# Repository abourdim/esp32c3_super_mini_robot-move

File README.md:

# 🤖 esp32c3_super_mini_robot-move — b3 on the `30_esp32_c3_move` board

A port of [`esp32c3_super_mini_robot-bit-rxy`](https://github.com/abourdim/esp32c3_super_mini_robot-bit-rxy)
("b3") onto the **`30_esp32_c3_move`** carrier board, plus a panning sonar head
the original does not have. Driven over Bluetooth Low Energy from the
[rxy web app](https://github.com/abourdim/rxy_web) — no install, no account, no
WiFi.

**The robot owns the layout.** The app is a generic renderer: it connects, asks
the robot for its panel, and draws whatever comes back. There is no per-robot
build of the app.

## Faithful to b3

Every module b3 has is still in the tree — buzzer, NeoPixels, battery sense,
board LEDs, OLED, both NeoPixel demos, all eight panels. Nothing was deleted.
What changed is the pin map, because the two carrier boards share an MCU and
nothing else.

What is **not fitted** on this build is switched off at a single `#define`
each, so it compiles out rather than failing at runtime:

| feature | b3 | here | state |
|---|---|---|---|
| left / right drive servo | GPIO 6 / 3 | **5 / 10** — J5 / J12, level-shifted | ✅ |
| HC-SR04 | 21 / 20 | **6 / 7** — J10, level-shifted | ✅ |
| head servo | *(none)* | **1** — J6 | ✅ |
| button / OTA | 0 (module BOOT) | **3** — SW1 | ✅ |
| green / red LED | 1 / 10 | **0 / 21** — J7 / J8 | ✅ |
| NeoPixel strip | 5 (or 10) | 20 — J9 | `CONFIG_NEOPIXELS_ENABLED 0` |
| buzzer | 4 | 4 — SW2 pads | `CONFIG_BUZZER_ENABLED 0` |
| battery sense | 4 | 4 — SW2 pads, **no divider on the board** | reads meaningless |
| OLED | I²C 8 / 9 | 8 / 9 — module pads, **not wired** | `CONFIG_OLED_ENABLED 0` |

Turning the strip off is worth more than it looks: its default French-flag
effect calls `delay(1000/60)` on **every** `loop()` iteration, so an absent
strip still paced the whole robot at 60 Hz to animate nothing.

The OLED keeps its runtime presence-probe for the day the wires go on, but with
the feature off nothing touches the I²C bus at all — not even the five-second
re-probe, which would otherwise poke a dead bus forever. Set
`CONFIG_OLED_ENABLED 1` once SDA/SCL/3V3/GND are on the module's pads; nothing
else needs changing. Wiring and the strapping-pin reasoning:
[`02_hardware/README.md`](02_hardware/README.md#attaching-the-oled).

Board source and the full netlist-derived pin map: [`02_hardware/`](02_hardware/).

## Three servos need four PWM timers

b3 allocates **one** LEDC timer and attaches two servos, which exactly fits.
The head makes three, and ESP32Servo does not warn when it runs short — it
prints `All PWM timers allocated! Can't accomodate 50.000 Hz` and **halts
inside `attach()`**, so `setup()` never returns.

That failure is invisible from outside. NimBLE has already started on its own
task by then, so the robot still advertises and the app still connects; it just
never answers anything, because `remotexy_handler()` lives in `loop()` and
`loop()` has never run. It presents as a protocol bug and is not one.

`setup()` now allocates all four.

## The 3-pin headers double as FET gates

J6, J7, J8 and J9 carry the same nets as Q1–Q4's gates, which drive the J1–J4
screw terminals and their yellow indicator LEDs. Anything plugged into a 3-pin
header switches its paired screw terminal in sympathy, so **leave J1–J4
unpopulated**. The upside is free activity indicators: D6–D9 light along with
whatever is on the header, so the link LEDs are visible even with nothing
plugged in.

## Why the button moved off GPIO 0

b3 uses the SuperMini's own BOOT button for the three-second OTA hold, and that
button exists here too. But on this board GPIO 0 is Q2's gate, so the gesture
would switch the J2 output on for the length of the hold — and GPIO 0 is more
useful as the green LED. SW1 is a real button with its own pull-up that drives
nothing else.

## Drive direction

`CONFIG_SERVO_INVERT_DRIVE` flips both channels. Both wheels ran backwards on
this chassis — that is motor polarity, not a left/right mix-up, and swapping
the two pins would have given a robot that spins instead. The flip is applied
to the command before the mix becomes pulses, so trim and the speed cap stay in
the frame they were written for, and it corrects the steering with it: with the
polarity wrong, a spin-left command was coming out as spin-right.

## The head, the radar, and sweep

The head servo is the one thing here that b3 does not have. It gives the app's
**radar** widget a bearing to plot against — the radar carries no value of its
own, it reads the distance gauge and the head slider by id.

**Sweep** is a toggle in the DISTANCE group. The head steps one notch per
telemetry pass rather than on a timer of its own, and the step happens *after*
the pass has sent this cycle's distance and angle. That ordering is the point:
the radar plots (angle, distance) pairs, and stepping independently would paint
readings at bearings the sensor was not pointing at when they were taken. Each
step then gets a full 500 ms to settle before the next measurement. 15° steps
across 10–170° is about 5.5 s per sweep.

Reversal happens **at** each limit, not past it. `moveHead()` clamps anyway,
but bouncing off the clamp parks the head on its end stop for an extra pass
every sweep — a stutter on the scope, and a stalled servo while it lasts.

Dragging the slider takes the head off sweep, otherwise the servo fights you
and the slider snaps back on the next pass. Leaving sweep re-centres.

The bearing is published every telemetry pass. Without that the radar plots at
whatever `head` last reported, which was its default — the head would sweep and
the scope would show a beam frozen at 90°.

**Head trim** (`head_off`, plus H−1 / H+1 buttons) is mechanical centring: a
pan mount is glued or screwed on by hand, so commanding 90° almost never points
dead ahead. The offset is applied where the servo is *written*, not to the
bearing that gets reported — the radar has to plot where the sensor is really
aimed, which is the corrected direction. Like the wheel trims it lives in NVS,
because it describes how the robot was assembled rather than how it is being
driven; and like them it rides the save-settle, so dragging the slider across
its range costs one flash write rather than sixty.

`CONFIG_SERVO_HEAD_MIN` / `_MAX` are the **mechanical** limits of your pan
mount, not 0–180. Narrow them to what the mount clears — a servo told to go
past its stop sits there stalled, drawing full stall current off the same rail
as the C3.

## Panels

b3's eight, plus a ninth — **Radar** — switched with the **Level** selector;
the choice is kept in NVS. The Radar panel is one subsystem on its own: the
scope, the head slider, Sweep, the head trim, and the distance readout the
radar is plotting, so the panel explains itself — you can see the number each
blip came from.

The new level is appended to the enum rather than inserted, because the level
index lives in NVS: renumbering the existing entries would silently move an
upgraded robot to a different panel. And since every layout carries its own
copy of the selector's options, all nine blobs were rewritten — otherwise the
new level would be unreachable from wherever you happened to be.

Expert has been cut down to what this board actually has:

- **removed** — the DISPLAY group (no OLED) and the SOUND group (no buzzer)
- **removed** — the six strip widgets from LIGHTS; the two board LEDs stay,
  they are real, and their J7/J8 headers light the onboard yellows too
- **moved** — TRIM is no longer its own group; all eight widgets sit inside
  DRIVE, which is where you use them, tuning while driving and watching the pull
- **added** — the head slider, the sweep toggle, and the radar, in DISTANCE

> ⚠️ **`gen_test_layouts.py` writes `test_decls.h`, which nothing includes.**
> The live blobs are hardcoded in `03_bit-rxy.cpp`, so running the generator
> changes nothing that reaches the board. It needs a splice step — S2's
> `gen_layouts.py` has the logic to copy — or it should be deleted. Until then,
> layout edits go into the blobs directly.

## Build and flash

```bash
cd 01_software/01_app && pio run -e esp32-c3-devkitm-1 -t upload
```

After the first USB flash, hold **SW1 for 3 seconds** to enter WiFi OTA mode.
Hold to 8 seconds to forget the saved network. The device is reachable as
`wdiy-move`, and the setup AP is `WDIY-Robot-Setup`.

BLE device name is `diy_app_mv`, distinct from b3's `diy_app_b3` so the two are
told apart in the scanner when both are powered on in the same room.

**The image is at 91.5% of flash** — roughly 110 KB spare on the default
partition table. Enough for tuning, not for another subsystem.

Note that with native USB-CDC the serial monitor attaches *after* boot, so you
will usually see nothing at startup. That is normal, not a fault.

## Before you build one

Three board facts firmware cannot paper over — the long form is in
[`02_hardware/README.md`](02_hardware/README.md):

- **J1–J4 must stay unpopulated** while anything is on J6–J9. Same nets.
- **J6 has no level shifter.** J5, J12 and J10 run through the TXB0104 and get
  clean 5 V logic; J6 carries the raw 3.3 V pin. Most hobby servos accept that.
- **The servo rail needs 470–1000 µF** at the connectors, fed from the input
  terminal rather than through the SuperMini's 5 V pin. Three drive servos on a
  rail with 100 nF browns the C3 out mid-drive, which reads as a random reboot.

## Known issues

- **Trim is applied with the wrong sign**, inherited from b3. It is added to
  both wheels, but the right channel's pulse range is inverted, so a positive
  trim pushes the two wheels in *opposite* physical directions. With b3's
  defaults of `5`/`5` an idle robot slowly rotates on the spot. Either zero the
  two `CONFIG_SERVO_SPEED_STOP_*_OFFSET` values or port S2's fix (`10c1468`),
  which subtracts on the inverted side.
- **`01_software/01_app/02_web/`** is b3's site and still describes b3's pin
  map. Its Pages workflow is set to manual trigger only, so a push cannot
  publish a site that is wrong about this robot. Rewrite it before re-enabling.

## Wiki

A full illustrated walkthrough — clone, build, flash, verify, plus the board's
pin map and how the sweep is paced — is on the wiki in three languages:

- [Robot MV (English)](https://abourdim.github.io/wiki/robot-mv-en.html)
- [Robot MV (Français)](https://abourdim.github.io/wiki/robot-mv.html)
- [Robot MV (العربية)](https://abourdim.github.io/wiki/robot-mv-ar.html)

Powered by [Workshop-DIY.org](https://workshop-diy.org)

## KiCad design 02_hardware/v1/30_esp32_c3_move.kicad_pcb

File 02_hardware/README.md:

# 🔌 Hardware

KiCad source, PCB renders and fab output for **`30_esp32_c3_move`**, the board
this firmware targets. Upstream lives at `01_kicad/30_esp32_c3_move/`.

## Versions

| Version | Status | Folder |
|---|---|---|
| **v1** | ✅ **Current — fabricated, and what the firmware is written against** | [`v1/`](v1/) |
| v2 | 📝 Planning stub, not a revision | [`v2/`](v2/) |

**v2 is not a new board.** Its PCB is byte-identical to v1 and it carries the
same 98 components; the only differences are one schematic block nudged 14 mm,
a project rename, and a to-do note dated 02/06/2025:

> add 2 neo pixel · oled connector · buzzer · battery level · large soldering
> footprint for the transistor

None of those are implemented. It is kept here because it is where that plan is
written down, not because it builds anything different.

## The pin map, and where it came from

Read out of `v1/30_esp32_c3_move.kicad_pcb` by walking footprint pads to nets —
**not** from the schematic, which labels every net `gpio_NN` and records nothing
about what it drives. `00_config.h` is the firmware-side copy of this table.

| GPIO | Connector | Used for |
|---|---|---|
| 5 | J5, 3-pin, via TXB0104 | left drive servo |
| 10 | J12, 3-pin, via TXB0104 | right drive servo |
| 6 / 7 | J10, 4-pin, via TXB0104 | HC-SR04 trig / echo |
| 1 | J6, 3-pin, **raw 3.3 V** · also Q1 gate → J1 | head servo |
| 0 | J7, 3-pin · also Q2 gate → J2 | green LED |
| 21 | J8, 3-pin · also Q3 gate → J3 | red LED |
| 20 | J9, 3-pin · also Q4 gate → J4 | NeoPixel strip |
| 3 | SW1, 10k pull-up R10 | button, OTA hold |
| 4 | SW2, 10k pull-up R11 | 🔧 buzzer + battery sense, bodged to the pads |
| **2, 8, 9** | **nowhere — module pads only** | 🔧 OLED on 8/9, four wires |

The four 3-pin headers are the same nets as the FET gates, so anything on
J6–J9 switches its paired screw terminal too. **Leave J1–J4 unpopulated.** The
compensation is that D6–D9 become free activity indicators for whatever is on
the header.

Each switched output has a 1N4007 flyback (D1–D4), a 10k gate pull-down
(R6–R9) and a yellow state LED (D6–D9 + R1–R4). The SK12D07VG4 slide switch
gates the input rail; J11 (screw) and J13 (JST-PH) both feed it.

## Three things to know before building one

**The 3-pin headers share nets with the screw terminals.** GPIO 1 is Q1's gate
*and* J6's signal pin; the same pairing holds for J7/J2, J8/J3 and J9/J4. A
servo on J6 pulses the J1 output at 50 Hz and flickers D6 continuously; a load
on J1 makes the head twitch. Populate the header or the terminal, never both.
Firmware cannot arbitrate this — it is a copper fact.

**J6 has no level shifter.** J5, J12 and J10 all run through the TXB0104 and
get clean 5 V logic. J6 carries the raw 3.3 V pin. Most hobby servos accept
that; a fussy one is the case where this board bites.

**The servo rail needs bulk capacitance.** Three servos share `VCC` with the
ESP32 and v1 has only 100 nF on that rail. An SG90 pulls ~700 mA stalled with
a larger startup surge, and these are drive servos — they run constantly. Add
**470–1000 µF at the servo connectors**, and feed servo power straight from the
input terminal rather than through the SuperMini's 5 V pin, so servo current
does not run through the module. Without this the rail dips and the C3 browns
out mid-drive, which reads as a random reboot.

## Attaching the OLED

GPIO 2, 8 and 9 reach the SuperMini's pads and no connector, so the SSD1306 is
four wires soldered to the module itself. This is what v2's "oled connector"
note is meant to fix.

| OLED pin | goes to |
|---|---|
| SDA | module **GPIO 8** |
| SCL | module **GPIO 9** |
| VCC | module **3V3** — *not* 5V, see below |
| GND | any GND |

**Take VCC from 3V3, not 5V.** Most SSD1306 modules accept either, but the
module's own I2C pull-up resistors go to whatever you feed it. On 5V those
pull-ups would hold SDA and SCL at 5V, and the C3's GPIOs are not 5V tolerant.

**The pull-ups are also what make the board boot.** GPIO 8 and 9 are both
strapping pins on the ESP32-C3, and both need to be high at reset — GPIO 9 low
at reset is what selects download mode. The module's pull-ups hold them there,
which is exactly why this pin pair works on b3 too. Flashing still works
normally: the module's BOOT button pulls GPIO 9 low against the pull-up.

The firmware probes `0x3C` at boot and re-probes every five seconds while no
screen is answering, so a wire that makes contact late or works loose recovers
without a power cycle. Watch serial for `[OLED] found` or `[OLED] appeared on
the bus`. If you get neither, the usual cause is a module strapped to **0x3D**
instead of 0x3C — some boards have a solder jumper for it.

Powered by [Workshop-DIY.org](https://workshop-diy.org)

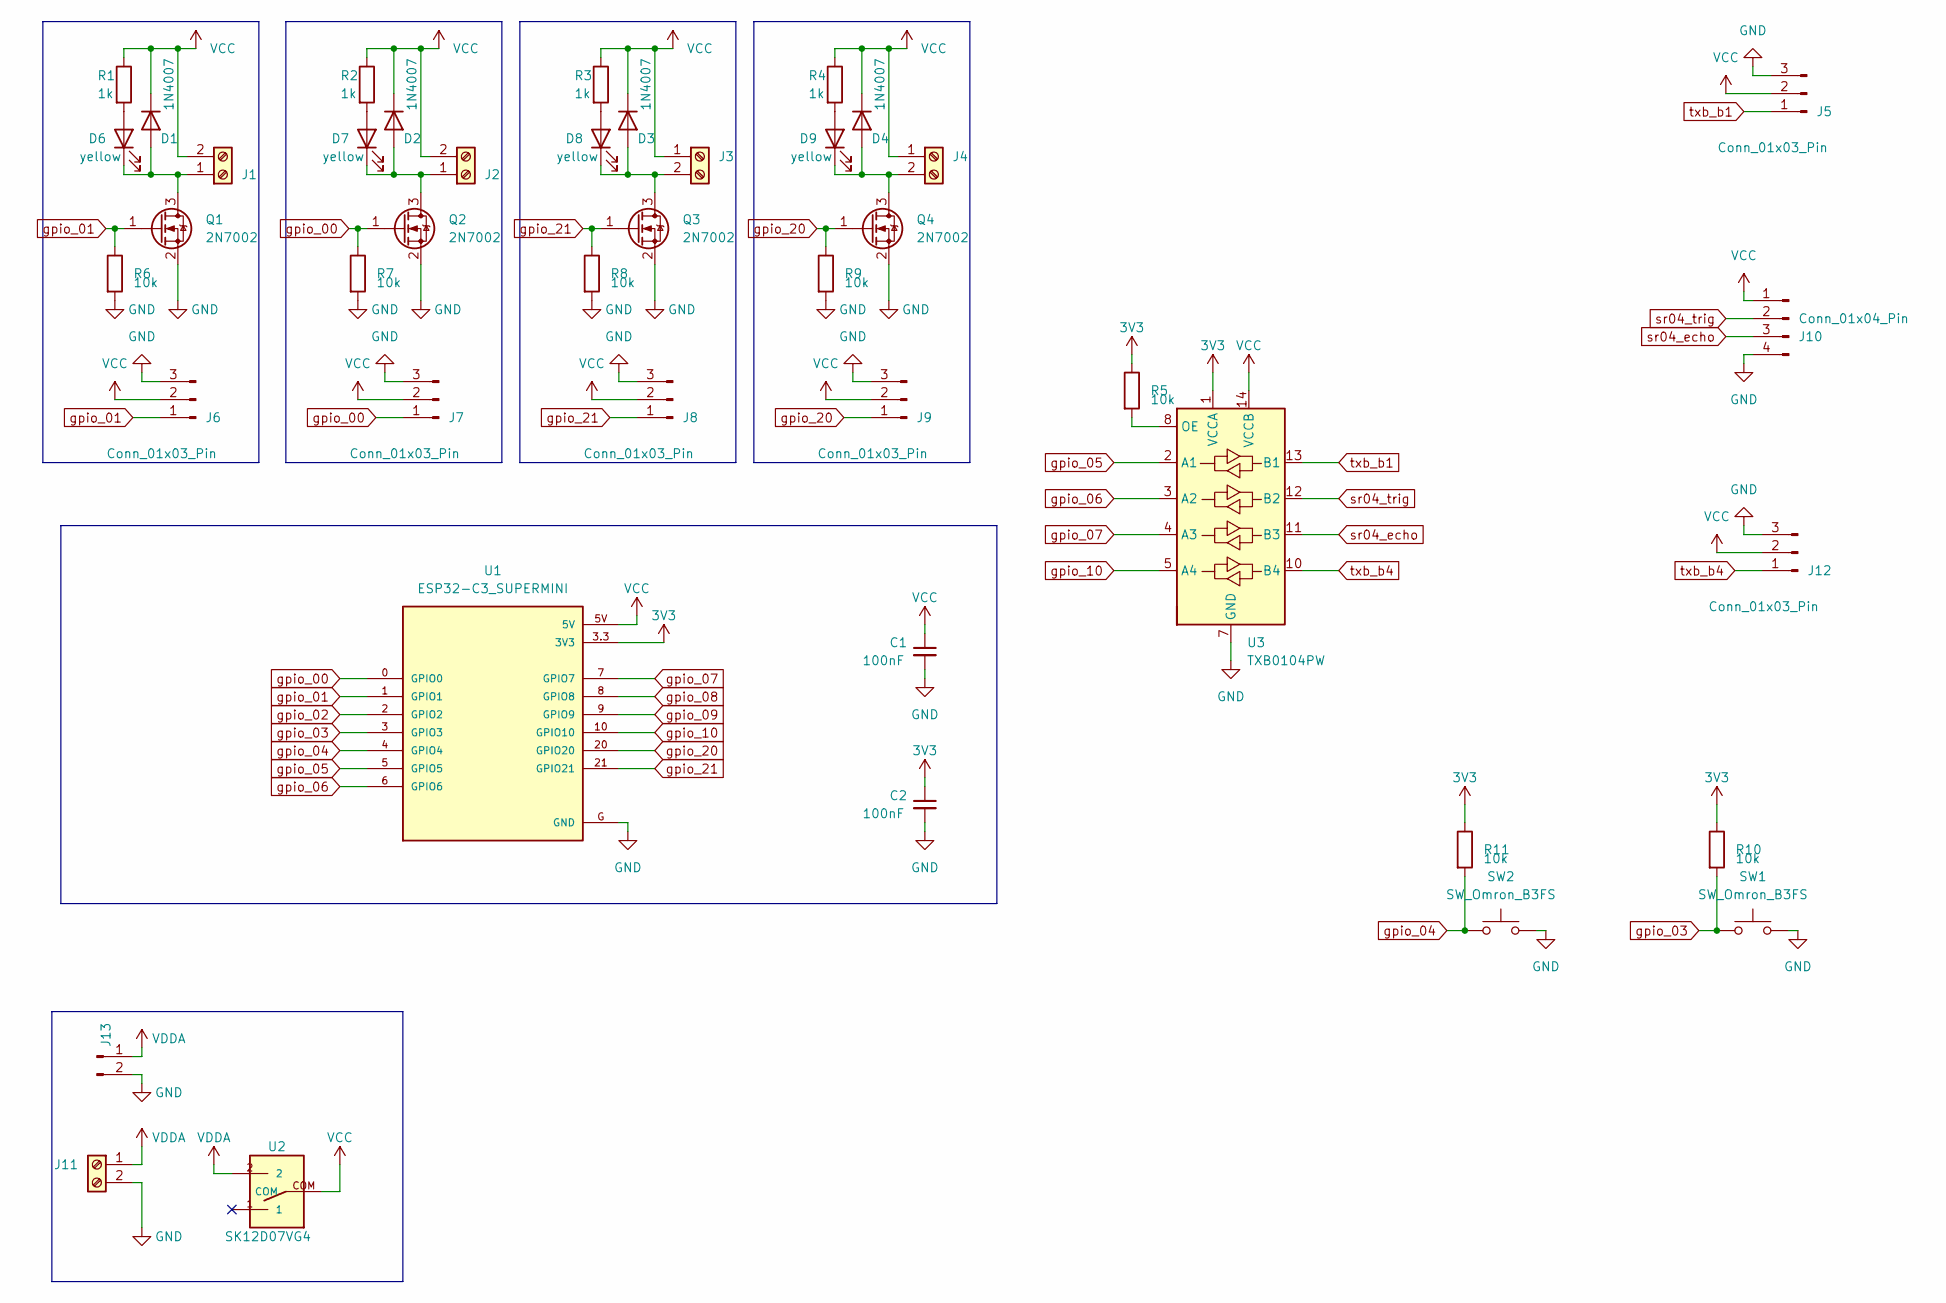
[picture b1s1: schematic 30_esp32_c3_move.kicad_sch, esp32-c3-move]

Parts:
C1, C2: 100nF; C_0805_2012Metric
D1, D2, D3, D4: 1N4007; D_SOD-123F
D6, D7, D8, D9: yellow; LED_0805_2012Metric_Pad1.15x1.40mm_HandSolder
J1, J2, J3, J4, J11: Screw_Terminal_01x02; TerminalBlock_Phoenix_MPT-0,5-2-2.54_1x02_P2.54mm_Horizontal
J5, J6, J7, J8, J9, J12: Conn_01x03_Pin; PinHeader_1x03_P2.54mm_Vertical
J10: Conn_01x04_Pin; PinHeader_1x04_P2.54mm_Vertical
J13: Conn_01x02_Pin; JST_PH_S2B-PH-K_1x02_P2.00mm_Horizontal
Q1, Q2, Q3, Q4: 2N7002; SOT-23_Handsoldering
R1, R2, R3, R4: 1k; R_0805_2012Metric
R5, R6, R7, R8, R9, R10, R11: 10k; R_0805_2012Metric
SW1, SW2: SW_Omron_B3FS; SW_Push_1P1T_NO_6x6mm_H9.5mm; lcsc C2837532
U1: ESP32-C3_SUPERMINI; MODULE_ESP32-C3_SUPERMINI
U2: SK12D07VG4
U3: TXB0104PW; TSSOP-14_4.4x5mm_P0.65mm

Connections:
3V3: C2.1, R5.1, R10.1, R11.1, U1.3.3 (3V3), U3.1 (VCCA)
GND: C1.2, C2.2, J5.3, J6.3, J7.3, J8.3, J9.3, J10.4, J11.2, J12.3, J13.2, Q1.2 (S), Q2.2 (S), Q3.2 (S), Q4.2 (S), R6.2, R7.2, R8.2, R9.2, SW1.2, SW2.2, U1.G (GND), U3.7 (GND)
unnamed: D1.2 (A), D6.1 (K), J1.1, Q1.3 (D)
unnamed: D2.2 (A), D7.1 (K), J2.1, Q2.3 (D)
unnamed: D3.2 (A), D8.1 (K), J3.2, Q3.3 (D)
unnamed: D4.2 (A), D9.1 (K), J4.2, Q4.3 (D)
unnamed: D6.2 (A), R1.2
unnamed: D7.2 (A), R2.2
unnamed: D8.2 (A), R3.2
unnamed: D9.2 (A), R4.2
unnamed: R5.2, U3.8 (OE)
VCC: C1.1, D1.1 (K), D2.1 (K), D3.1 (K), D4.1 (K), J1.2, J2.2, J3.1, J4.1, J5.2, J6.2, J7.2, J8.2, J9.2, J10.1, J12.2, R1.1, R2.1, R3.1, R4.1, U1.5V, U2.COM, U3.14 (VCCB)
VDDA: J11.1, J13.1, U2.2
gpio_00: J7.1, Q2.1 (G), R7.1, U1.0 (GPIO0)
gpio_01: J6.1, Q1.1 (G), R6.1, U1.1 (GPIO1)
gpio_02: U1.2 (GPIO2)
gpio_03: R10.2, SW1.1, U1.3 (GPIO3)
gpio_04: R11.2, SW2.1, U1.4 (GPIO4)
gpio_05: U1.5 (GPIO5), U3.2 (A1)
gpio_06: U1.6 (GPIO6), U3.3 (A2)
gpio_07: U1.7 (GPIO7), U3.4 (A3)
gpio_08: U1.8 (GPIO8)
gpio_09: U1.9 (GPIO9)
gpio_10: U1.10 (GPIO10), U3.5 (A4)
gpio_20: J9.1, Q4.1 (G), R9.1, U1.20 (GPIO20)
gpio_21: J8.1, Q3.1 (G), R8.1, U1.21 (GPIO21)
sr04_echo: J10.3, U3.11 (B3)
sr04_trig: J10.2, U3.12 (B2)
txb_b1: J5.1, U3.13 (B1)
txb_b4: J12.1, U3.10 (B4)

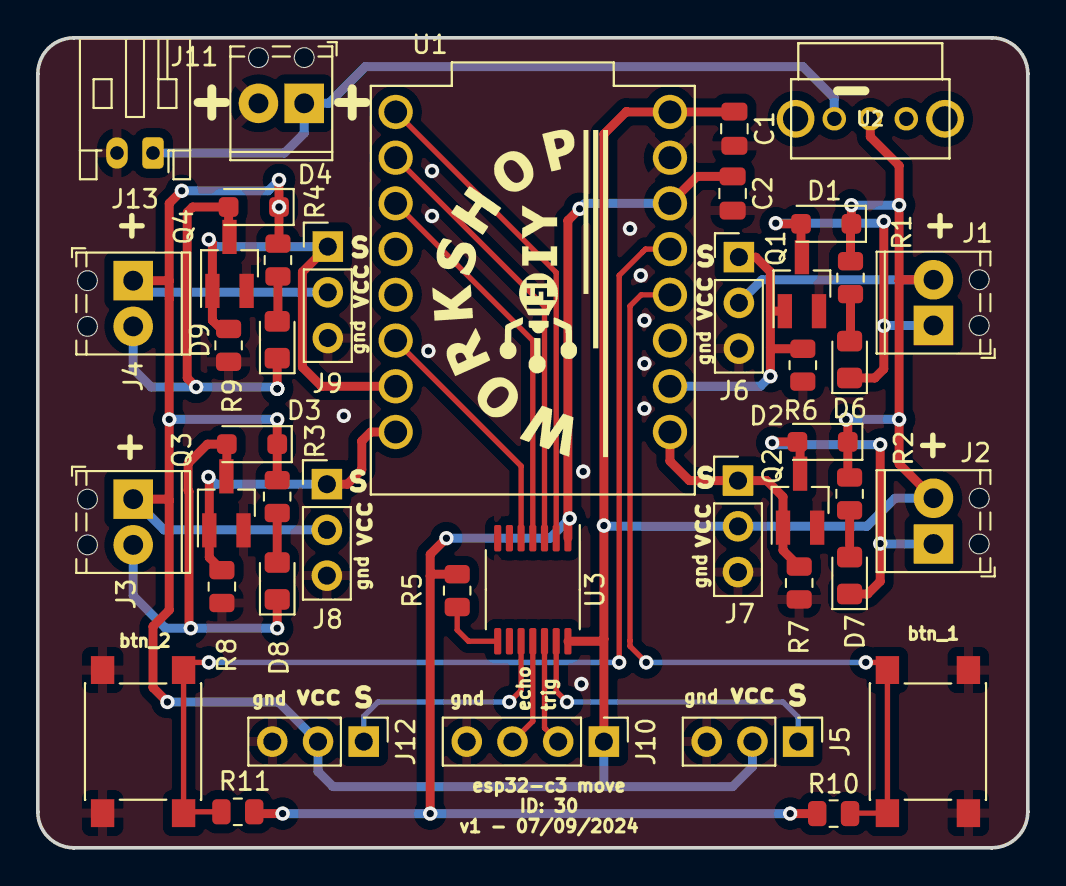
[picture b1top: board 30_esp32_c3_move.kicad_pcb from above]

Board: 2 copper layers, 55.0 x 45.0 mm, 43 parts (0 on the bottom side), 27 nets.

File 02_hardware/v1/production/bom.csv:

Designator,Footprint,Quantity,Value,LCSC Part #
"C1, C2",0805,2,100nF,
"D1, D2, D3, D4",D_SOD-123F,4,1N4007,
"D6, D7, D8, D9",0805,4,yellow,
"J1, J11, J2, J3, J4","TerminalBlock_Phoenix_MPT-0,5-2-2.54_1x02_P2.54mm_Horizontal",5,Screw_Terminal_01x02,
J10,PinHeader_1x04_P2.54mm_Vertical,1,Conn_01x04_Pin,
"J12, J5, J6, J7, J8, J9",PinHeader_1x03_P2.54mm_Vertical,6,Conn_01x03_Pin,
J13,JST_PH_S2B-PH-K_1x02_P2.00mm_Horizontal,1,Conn_01x02_Pin,
"Q1, Q2, Q3, Q4",SOT-23_Handsoldering,4,2N7002,
"R1, R2, R3, R4",0805,4,1k,
"R10, R11, R5, R6, R7, R8, R9",0805,7,10k,
"SW1, SW2",SW_Push_1P1T_NO_6x6mm_H9.5mm,2,SW_Omron_B3FS,
U1,MODULE_ESP32-C3_SUPERMINI,1,ESP32-C3_SUPERMINI,
U2,SK12D07VG4,1,SK12D07VG4,
U3,TSSOP-14_4.4x5mm_P0.65mm,1,TXB0104PW,

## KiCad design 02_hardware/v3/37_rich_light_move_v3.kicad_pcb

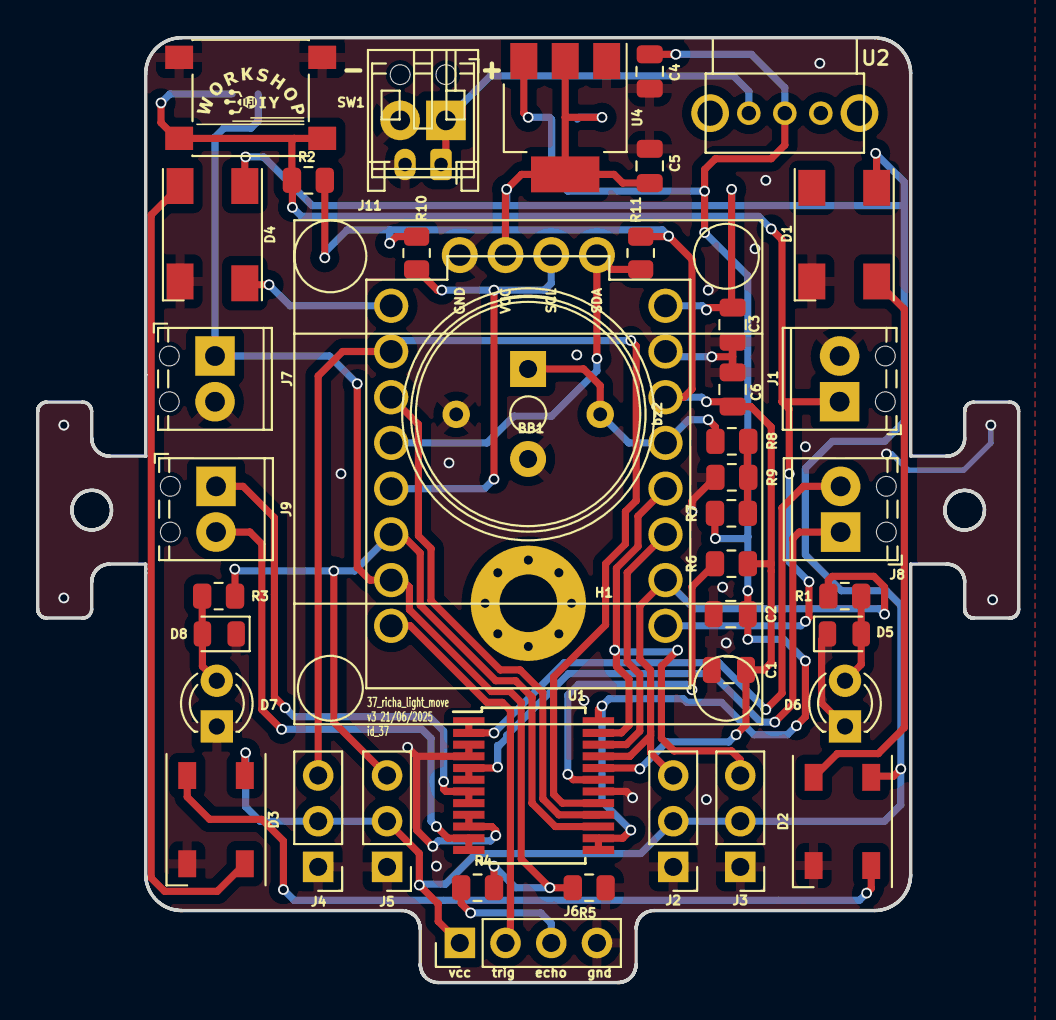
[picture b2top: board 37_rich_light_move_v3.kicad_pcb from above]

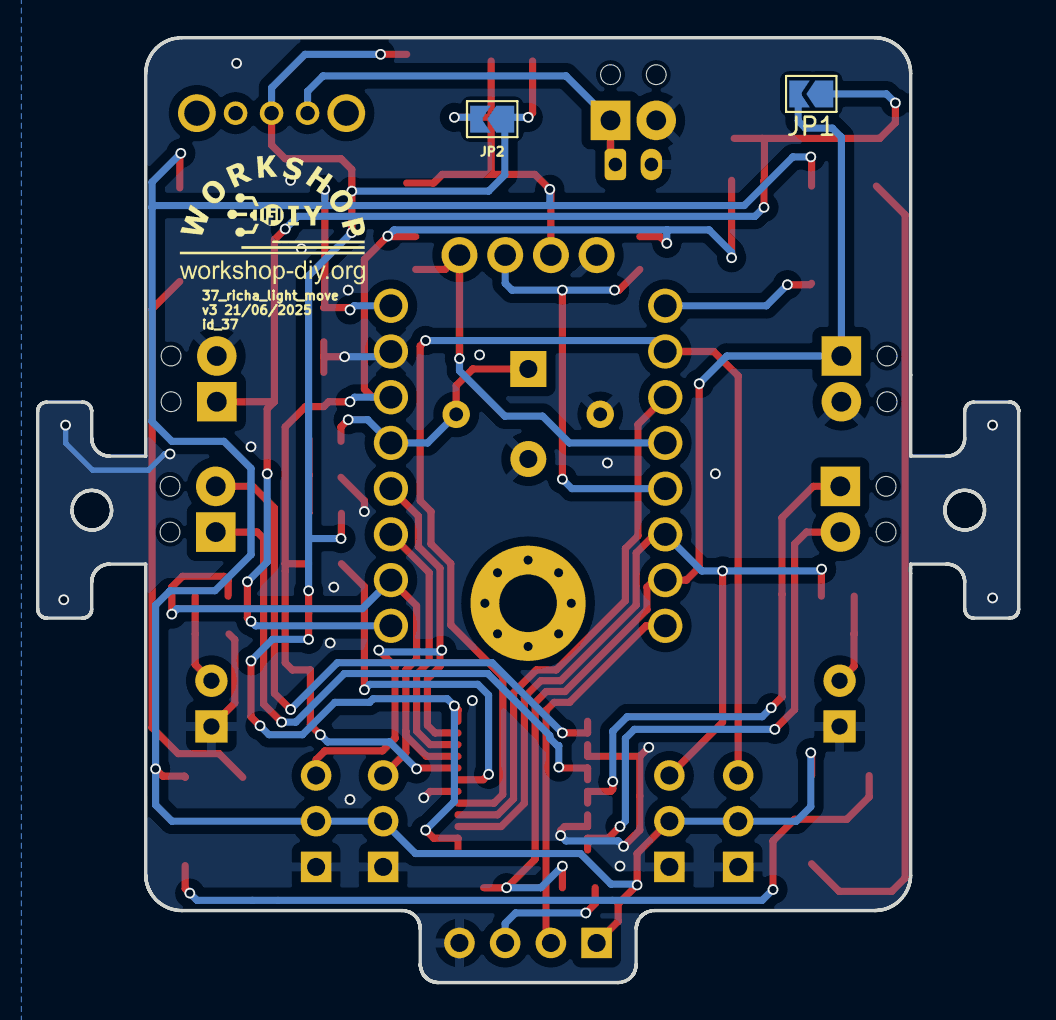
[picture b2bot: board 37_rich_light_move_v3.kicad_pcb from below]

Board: 2 copper layers, 54.5 x 52.5 mm, 47 parts (2 on the bottom side), 30 nets.

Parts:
BB1: oled_128x32; oled_128X64_no_holes
C1, C2, C3, C4, C5, C6: 100nF; C_0805_2012Metric
D1, D2, D3, D4: led_tx1812cxa_5050
D5: green; LED_0805_2012Metric
D6: green; LED_D3.0mm
D7: blue; LED_D3.0mm
D8: blue; LED_0805_2012Metric
H1: MountingHole; MountingHole_3.2mm_M3_Pad_Via
J1, J7, J8, J9, J11: Screw_Terminal_01x02; TerminalBlock_Phoenix_MPT-0,5-2-2.54_1x02_P2.54mm_Horizontal
J2, J3, J4, J5: Conn_01x03_Pin; PinHeader_1x03_P2.54mm_Vertical
J6: Conn_01x04_Pin; PinHeader_1x04_P2.54mm_Vertical
J10: Conn_01x02_Pin; JST_PH_S2B-PH-K_1x02_P2.00mm_Horizontal
JP1, JP2: SolderJumper_2_Open; SolderJumper-2_P1.3mm_Open_TrianglePad1.0x1.5mm
R1, R3, R8: 1k; R_0805_2012Metric
R2, R6, R7: 10k; R_0805_2012Metric
R4, R9: 4K7; R_0805_2012Metric
R5, R10, R11: 10K; R_0805_2012Metric
SW1: SW_Omron_B3FS; SW_Push_1P1T_NO_6x6mm_H9.5mm
U1: TB6612FNG; SSOP-24_5.3x8.2mm_P0.65mm
U2: SK12D07VG4
U3: ESP32-C3_SUPERMINI; MODULE_ESP32-C3_SUPERMINI
U4: AMS1117-5.0; SOT-223-3_TabPin2
bz1: buzz_8x14
bz2: BUZZER; Buzzer_TDK_PS1240P02BT_D12.2mm_H6.5mm

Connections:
3V3: C1.1, C6.1, R2.1, R6.1, R10.1, R11.1, U1.20 (VCC), U3.3.3 (3V3)
5V: BB1.2 (VCC), C3.1, C5.1, D1.1 (VDD), D2.1 (VDD), D3.1 (VDD), D4.1 (VDD), J2.2, J3.2, J4.2, J5.2, J6.1, JP2.2 (B), U3.5V, U4.2 (VO)
GND: BB1.1 (GND), C1.2, C2.2, C3.2, C4.2, C5.2, C6.2, D1.3 (GND), D2.3 (GND), D3.3 (GND), D4.3 (GND), D5.1 (K), D6.1 (K), D7.1 (K), D8.1 (K), J1.2, J2.1, J3.1, J4.1, J5.1, J6.4, J7.2, J10.2, J11.2, R5.2, R9.2, SW1.2, U1.3 (PGND1), U1.4 (PGND1), U1.9 (PGND2), U1.10 (PGND2), U1.18 (GND), U3.G (GND), U4.1 (GND), bz1.1, bz2.2 (GND)
unnamed: D1.4 (DIN), D2.2 (DOUT)
unnamed: D2.4 (DIN), D3.2 (DOUT)
unnamed: D3.4 (DIN), D4.2 (DOUT)
unnamed: D5.2 (A), D6.2 (A), R1.2
unnamed: D7.2 (A), D8.2 (A), R3.2
unnamed: J6.3, R4.1
unnamed: J8.1, U1.5 (AO2), U1.6 (AO2)
unnamed: J8.2, U1.1 (AO1), U1.2 (AO1)
unnamed: J9.1, U1.7 (BO2), U1.8 (BO2)
unnamed: J9.2, U1.11 (BO1), U1.12 (BO1)
unnamed: R7.2, R8.1, R9.1
unnamed: R6.2, U1.19 (STBY)
VCC: C2.1, C4.1, JP2.1 (A), R7.1, U1.13 (VM2), U1.14 (VM3), U1.24 (VM1), U2.COM, U4.3 (VI)
VDDA: J10.1, J11.1, U2.2
gpio_00: J1.1, JP1.1 (A), R2.2, SW1.1, U3.0 (GPIO0)
gpio_01: J2.3, R1.1, U1.21 (AIN1), U3.1 (GPIO1)
gpio_02: U1.22 (AIN2), U3.2 (GPIO2)
gpio_03: J3.3, U1.23 (PWMA), U3.3 (GPIO3)
gpio_04: R8.2, U3.4 (GPIO4), bz1.2, bz2.1 (POS)
gpio_05: D4.4 (DIN), U3.5 (GPIO5)
gpio_06: J4.3, U1.17 (BIN1), U3.6 (GPIO6)
gpio_07: U1.16 (BIN2), U3.7 (GPIO7)
gpio_08: BB1.4 (SDA), R11.2, U3.8 (GPIO8)
gpio_09: BB1.3 (SCL), R10.2, U3.9 (GPIO9)
gpio_10: J5.3, R3.1, U1.15 (PWMB), U3.10 (GPIO10)
gpio_20: J7.1, JP1.2 (B), R4.2, R5.1, U3.20 (GPIO20)
gpio_21: J6.2, U3.21 (GPIO21)

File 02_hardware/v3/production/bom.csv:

Designator,Footprint,Quantity,Value,LCSC Part #
BB1,oled_128X64_no_holes,1,oled_128x32,
BZ1,buzz_8x14,1,buzz_8x14,
BZ2,Buzzer_TDK_PS1240P02BT_D12.2mm_H6.5mm,1,BUZZER,
"C1, C2, C3, C4, C5, C6",0805,6,100nF,
"D1, D2, D3, D4",led_tx1812cxa_5050,4,led_tx1812cxa_5050,
D5,0805,1,green,
D6,LED_D3.0mm,1,green,
D7,LED_D3.0mm,1,blue,
D8,0805,1,blue,
H1,MountingHole_3.2mm_M3_Pad_Via,1,MountingHole,
"J1, J11, J7, J8, J9","TerminalBlock_Phoenix_MPT-0,5-2-2.54_1x02_P2.54mm_Horizontal",5,Screw_Terminal_01x02,
J10,JST_PH_S2B-PH-K_1x02_P2.00mm_Horizontal,1,Conn_01x02_Pin,
"J2, J3, J4, J5",PinHeader_1x03_P2.54mm_Vertical,4,Conn_01x03_Pin,
J6,PinHeader_1x04_P2.54mm_Vertical,1,Conn_01x04_Pin,
"JP1, JP2",SolderJumper-2_P1.3mm_Open_TrianglePad1.0x1.5mm,2,SolderJumper_2_Open,
"R1, R3, R8",0805,3,1k,
"R10, R11, R2, R5, R6, R7",0805,6,10K,
"R4, R9",0805,2,4K7,
SW1,SW_Push_1P1T_NO_6x6mm_H9.5mm,1,SW_Omron_B3FS,
U1,SSOP-24_5.3x8.2mm_P0.65mm,1,TB6612FNG,
U2,SK12D07VG4,1,SK12D07VG4,
U3,MODULE_ESP32-C3_SUPERMINI,1,ESP32-C3_SUPERMINI,
U4,SOT-223-3_TabPin2,1,AMS1117-5.0,

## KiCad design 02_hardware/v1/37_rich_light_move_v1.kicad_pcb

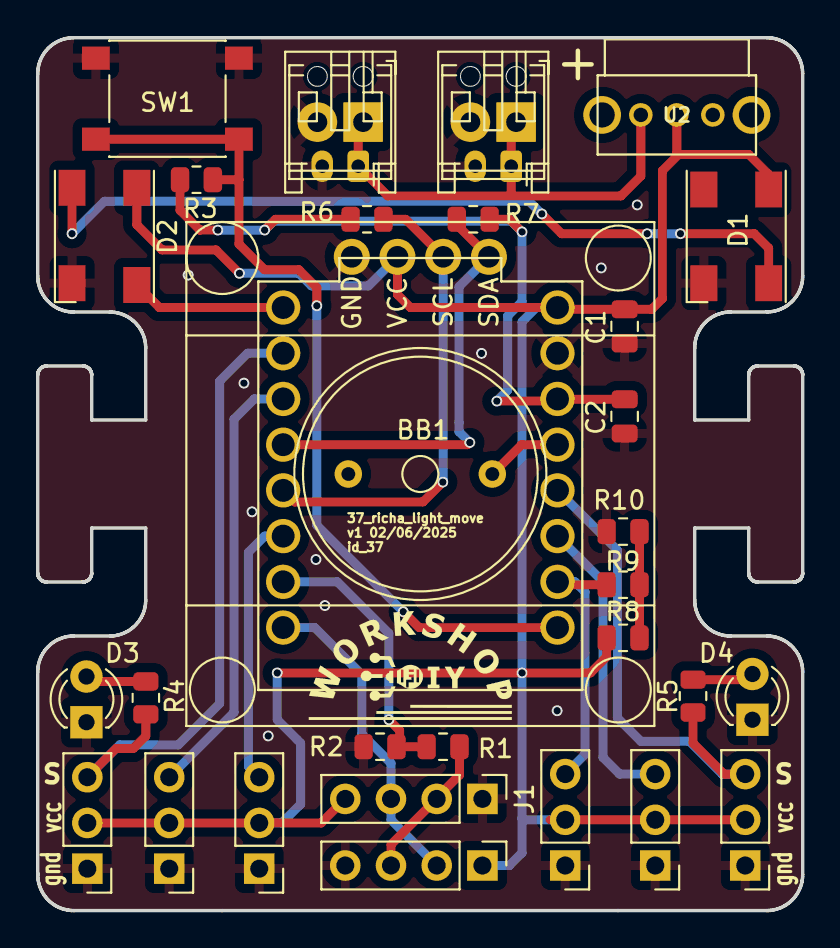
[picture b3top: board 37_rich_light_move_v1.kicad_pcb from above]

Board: 2 copper layers, 42.5 x 48.5 mm, 33 parts (0 on the bottom side), 22 nets.

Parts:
BB1: oled_128x32; oled_128X64_no_holes
C1, C2: 100nF; C_0805_2012Metric
D1, D2: led_tx1812cxa_5050
D3, D4: yellow; LED_D3.0mm
J1, J2: Conn_01x04_Pin; PinHeader_1x04_P2.54mm_Vertical
J3, J4, J5, J6, J7, J8: Conn_01x03_Pin; PinHeader_1x03_P2.54mm_Vertical
J9, J10: Conn_01x02_Pin; JST_PH_S2B-PH-K_1x02_P2.00mm_Horizontal
J11, J12: Screw_Terminal_01x02; TerminalBlock_Phoenix_MPT-0,5-2-2.54_1x02_P2.54mm_Horizontal
R1: 4K7; R_0805_2012Metric
R2, R6, R7: 10K; R_0805_2012Metric
R3, R8, R10: 10k; R_0805_2012Metric
R4, R5, R9: 1k; R_0805_2012Metric
SW1: SW_Omron_B3FS; SW_Push_1P1T_NO_6x6mm_H9.5mm
U1: ESP32-C3_SUPERMINI; MODULE_ESP32-C3_SUPERMINI
U2: SK12D07VG4
bz1: buzz_8x14

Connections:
3V3: C2.1, R3.1, R6.1, R7.1, U1.3.3 (3V3)
GND: BB1.1 (GND), C1.2, C2.2, D1.3 (GND), D2.3 (GND), D3.1 (K), D4.1 (K), J1.1, J2.4, J3.1, J4.1, J5.1, J6.1, J7.1, J8.1, J9.2, J10.2, J11.2, J12.2, R2.2, R10.2, SW1.2, U1.G (GND), bz1.1
unnamed: D1.4 (DIN), D2.2 (DOUT)
unnamed: D3.2 (A), R4.2
unnamed: D4.2 (A), R5.2
unnamed: J1.2, J2.3, R1.1
unnamed: R8.2, R9.1, R10.1
VCC: BB1.2 (VCC), C1.1, D1.1 (VDD), D2.1 (VDD), J1.4, J2.1, J3.2, J4.2, J5.2, J6.2, J7.2, J8.2, R8.1, U1.5V, U2.COM
VDDA: J9.1, J10.1, J11.1, J12.1, U2.2
gpio_00: R3.2, SW1.1, U1.0 (GPIO0)
gpio_01: J7.3, R9.2, U1.1 (GPIO1)
gpio_02: J3.3, U1.2 (GPIO2)
gpio_03: J8.3, R5.1, U1.3 (GPIO3)
gpio_04: U1.4 (GPIO4), bz1.2
gpio_05: D2.4 (DIN), U1.5 (GPIO5)
gpio_06: J4.3, R4.1, U1.6 (GPIO6)
gpio_07: J5.3, U1.7 (GPIO7)
gpio_08: BB1.4 (SDA), R7.2, U1.8 (GPIO8)
gpio_09: BB1.3 (SCL), R6.2, U1.9 (GPIO9)
gpio_10: J6.3, U1.10 (GPIO10)
gpio_20: R1.2, R2.1, U1.20 (GPIO20)
gpio_21: J1.3, J2.2, U1.21 (GPIO21)

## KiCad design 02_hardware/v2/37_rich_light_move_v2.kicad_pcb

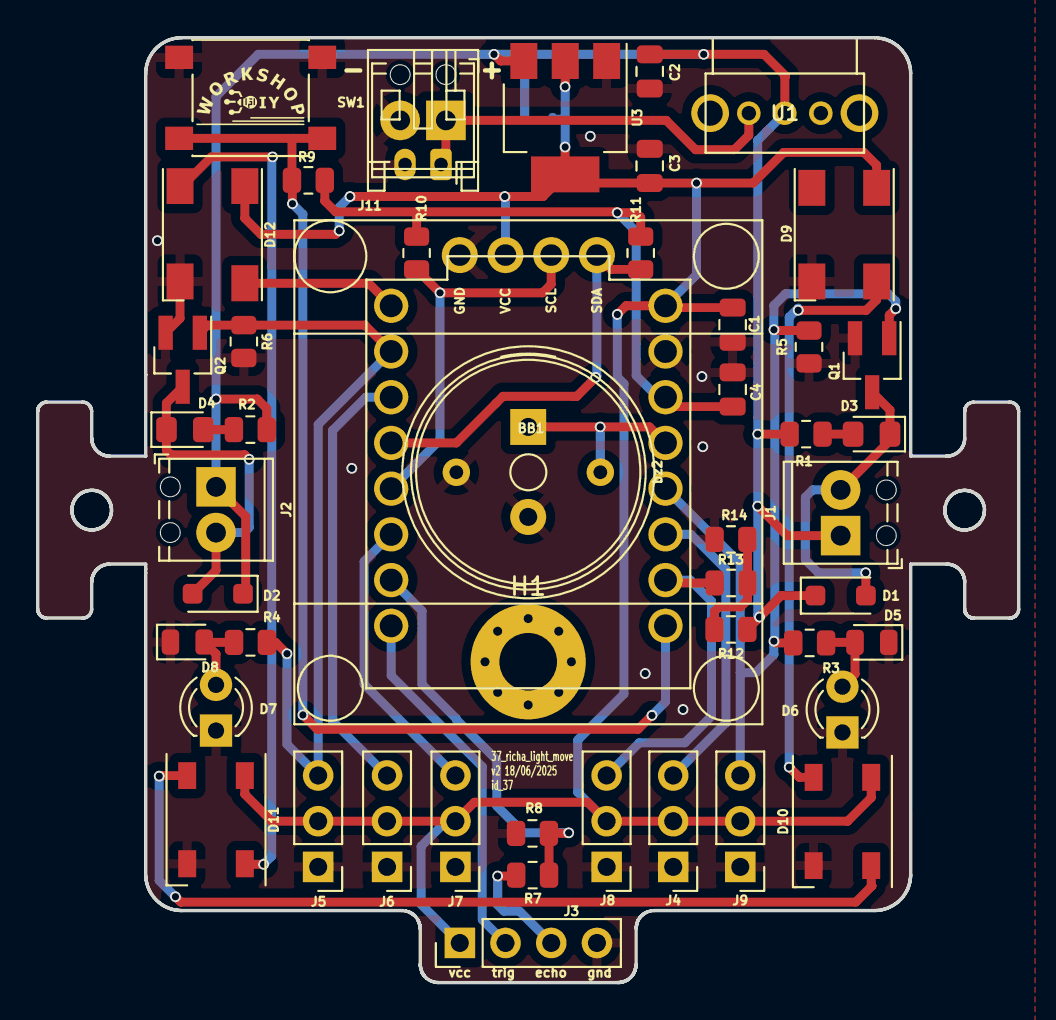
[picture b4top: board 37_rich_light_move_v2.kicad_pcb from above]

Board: 2 copper layers, 54.5 x 52.5 mm, 52 parts (1 on the bottom side), 29 nets.

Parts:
BB1: oled_128x32; oled_128X64_no_holes
C1, C2, C3, C4: 100nF; C_0805_2012Metric
D1, D2: 1N4007; D_SOD-123F
D3, D4: yellow; LED_0805_2012Metric_Pad1.15x1.40mm_HandSolder
D5: green; LED_0805_2012Metric
D6: green; LED_D3.0mm
D7: blue; LED_D3.0mm
D8: blue; LED_0805_2012Metric
D9, D10, D11, D12: led_tx1812cxa_5050
H1: MountingHole; MountingHole_3.2mm_M3_Pad_Via
J1, J2, J11: Screw_Terminal_01x02; TerminalBlock_Phoenix_MPT-0,5-2-2.54_1x02_P2.54mm_Horizontal
J3: Conn_01x04_Pin; PinHeader_1x04_P2.54mm_Vertical
J4, J5, J6, J7, J8, J9: Conn_01x03_Pin; PinHeader_1x03_P2.54mm_Vertical
J10: Conn_01x02_Pin; JST_PH_S2B-PH-K_1x02_P2.00mm_Horizontal
JP1: SolderJumper_2_Open; SolderJumper-2_P1.3mm_Open_TrianglePad1.0x1.5mm
Q1, Q2: 2N7002; SOT-23_Handsoldering
R1, R2, R3, R4, R13: 1k; R_0805_2012Metric
R5, R6, R9, R12: 10k; R_0805_2012Metric
R7, R14: 4K7; R_0805_2012Metric
R8, R10, R11: 10K; R_0805_2012Metric
SW1: SW_Omron_B3FS; SW_Push_1P1T_NO_6x6mm_H9.5mm
U1: SK12D07VG4
U2: ESP32-C3_SUPERMINI; MODULE_ESP32-C3_SUPERMINI
U3: AMS1117-5.0; SOT-223-3_TabPin2
bz1: buzz_8x14
bz2: BUZZER; Buzzer_TDK_PS1240P02BT_D12.2mm_H6.5mm

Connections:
3V3: C4.1, R9.1, R10.1, R11.1, U2.3.3 (3V3)
5V: BB1.2 (VCC), C1.1, C3.1, D9.1 (VDD), D10.1 (VDD), D11.1 (VDD), D12.1 (VDD), J3.1, J4.2, J5.2, J6.2, J7.2, J8.2, J9.2, JP1.2 (B), U2.5V, U3.2 (VO)
GND: BB1.1 (GND), C1.2, C2.2, C3.2, C4.2, D5.1 (K), D6.1 (K), D7.1 (K), D8.1 (K), D9.3 (GND), D10.3 (GND), D11.3 (GND), D12.3 (GND), J3.4, J4.1, J5.1, J6.1, J7.1, J8.1, J9.1, J10.2, J11.2, Q1.2 (S), Q2.2 (S), R5.2, R6.2, R8.2, R14.2, SW1.2, U2.G (GND), U3.1 (GND), bz1.1, bz2.2 (GND)
unnamed: D1.2 (A), D3.1 (K), J1.2, Q1.3 (D)
unnamed: D2.2 (A), D4.1 (K), J2.2, Q2.3 (D)
unnamed: D3.2 (A), R1.2
unnamed: D4.2 (A), R2.2
unnamed: D5.2 (A), D6.2 (A), R3.2
unnamed: D7.2 (A), D8.2 (A), R4.2
unnamed: D10.4 (DIN), D11.2 (DOUT)
unnamed: D9.4 (DIN), D10.2 (DOUT)
unnamed: D11.4 (DIN), D12.2 (DOUT)
unnamed: J3.3, R7.1
unnamed: R12.2, R13.1, R14.1
VCC: C2.1, D1.1 (K), D2.1 (K), J1.1, J2.1, JP1.1 (A), R1.1, R2.1, R12.1, U1.COM, U3.3 (VI)
VDDA: J10.1, J11.1, U1.2
gpio_00: R9.2, SW1.1, U2.0 (GPIO0)
gpio_01: J8.3, R13.2, U2.1 (GPIO1)
gpio_02: J4.3, U2.2 (GPIO2)
gpio_03: J9.3, Q1.1 (G), R3.1, R5.1, U2.3 (GPIO3)
gpio_04: U2.4 (GPIO4), bz1.2, bz2.1 (POS)
gpio_05: D12.4 (DIN), U2.5 (GPIO5)
gpio_06: J5.3, Q2.1 (G), R4.1, R6.1, U2.6 (GPIO6)
gpio_07: J6.3, U2.7 (GPIO7)
gpio_08: BB1.4 (SDA), R11.2, U2.8 (GPIO8)
gpio_09: BB1.3 (SCL), R10.2, U2.9 (GPIO9)
gpio_10: J7.3, U2.10 (GPIO10)
gpio_20: R7.2, R8.1, U2.20 (GPIO20)
gpio_21: J3.2, U2.21 (GPIO21)

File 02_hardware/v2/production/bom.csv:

Designator,Footprint,Quantity,Value,LCSC Part #
BB1,oled_128X64_no_holes,1,oled_128x32,
BZ1,buzz_8x14,1,buzz_8x14,
BZ2,Buzzer_TDK_PS1240P02BT_D12.2mm_H6.5mm,1,BUZZER,
"C1, C2, C3, C4",0805,4,100nF,
"D1, D2",D_SOD-123F,2,1N4007,
"D10, D11, D12, D9",led_tx1812cxa_5050,4,led_tx1812cxa_5050,
"D3, D4",0805,2,yellow,
D5,0805,1,green,
D6,LED_D3.0mm,1,green,
D7,LED_D3.0mm,1,blue,
D8,0805,1,blue,
H1,MountingHole_3.2mm_M3_Pad_Via,1,MountingHole,
"J1, J11, J2","TerminalBlock_Phoenix_MPT-0,5-2-2.54_1x02_P2.54mm_Horizontal",3,Screw_Terminal_01x02,
J10,JST_PH_S2B-PH-K_1x02_P2.00mm_Horizontal,1,Conn_01x02_Pin,
J3,PinHeader_1x04_P2.54mm_Vertical,1,Conn_01x04_Pin,
"J4, J5, J6, J7, J8, J9",PinHeader_1x03_P2.54mm_Vertical,6,Conn_01x03_Pin,
JP1,SolderJumper-2_P1.3mm_Open_TrianglePad1.0x1.5mm,1,SolderJumper_2_Open,
"Q1, Q2",SOT-23_Handsoldering,2,2N7002,
"R1, R13, R2, R3, R4",0805,5,1k,
"R10, R11, R12, R5, R6, R8, R9",0805,7,10K,
"R14, R7",0805,2,4K7,
SW1,SW_Push_1P1T_NO_6x6mm_H9.5mm,1,SW_Omron_B3FS,
U1,SK12D07VG4,1,SK12D07VG4,
U2,MODULE_ESP32-C3_SUPERMINI,1,ESP32-C3_SUPERMINI,
U3,SOT-223-3_TabPin2,1,AMS1117-5.0,
